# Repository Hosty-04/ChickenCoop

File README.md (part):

# Kurník

Systém pro automatizaci kurníku s detekcí snesených vajec - bakalářská práce

## Zadání

- Prostudujte možnosti automatizace uzavírání kurníku, možné metody detekce snesených vajec a dostupné možnosti komunikace a připojení zařízení do IoT sítě (např. NB-IoT, WiFi, LoRaWAN).
- Navrhněte systém pro automatické otevírání a uzavírání dvířek kurníku s možností rozšíření o jednotky se senzory ve snáškových hnízdech (min. 5 hnízd). Prostudujte možnosti napájení z akumulátoru nebo fotovoltaického panelu. Proveďte analýzu možnosti přenosu dat do cloudu a jejich zobrazení uživateli včetně historie snášek a možnosti vzdáleného ovládání, například skrze aplikaci.
- Na základě analýzy navrhněte způsob vzdálené uživatelské interakce pro zobrazení stavu dvířek, manuální ovládání a počítání snesených vajec.
- Navrhněte schéma zařízení, které bude obsahovat mikrořadič, komunikační modul, senzory, řízení dvířek, napájecí/nabíjecí obvody. Dbejte na nízký příkon celého zařízení. Proveďte návrh desky plošných spojů.
- Zkonstruujte hardwarovou realizaci navrženého systému. Osaďte a zprovozněte řídicí elektroniku. Vytvořte ovládací firmware. Realizujte přenos dat ze zařízení k uživateli včetně ovládacího rozhraní a možnosti zobrazení historie.
- Ověřte funkčnost systému experimentálním měřením a vyhodnoťte spolehlivost detekce a ovládání.
- Zveřejněte veškeré výrobní podklady na vhodné platformě (např. GitHub).

## Schémata

## Elektronika

<br>

<picture>
  <source media="(prefers-color-scheme: dark)" srcset="Schematics/block_schematic_electronics_white.png">
  <source media="(prefers-color-scheme: light)" srcset="Schematics/block_schematic_electronics_black.png">
  
</picture>

## Komunikace

<br>

<picture>
  <source media="(prefers-color-scheme: dark)" srcset="Schematics/block_schematic_comms_white.png">
  <source media="(prefers-color-scheme: light)" srcset="Schematics/block_schematic_comms_black.png">
  
</picture>

<br><br>

> Uživatelské příkazy cestují opačným směrem

## Popis

### 1) Mechanika

### a) Krabičky

Solární panel je uchycen v rámečku vytištěném z materiálu PETG, jehož vnější rozměr (360 × 240 mm) přesahuje rozměr panelu (340 × 220 mm) o 10 mm po každé straně. Tento materiál byl zvolen pro jeho vysokou houževnatost a teplotní odolnost. Kapsa pro panel je hluboká 4 mm, tedy o 1 mm více než tloušťka panelu, aby panel po vložení mírně zapadl pod úroveň okraje rámečku a nedocházelo k zadržování vody na jeho povrchu. Dno kapsy je opatřeno výřezem o rozměru 320 × 200 mm, odpovídajícím aktivní ploše panelu, takže rámeček má tvar pasparty a nestíní dopadající sluneční záření. Po vložení panelu do kapsy je spára mezi jeho okrajem a stěnou rámečku vyplněna venkovním UV odolným silikonovým tmelem, čímž vzniká vodotěsné a zároveň mechanicky pevné spojení bez nutnosti vrtat do samotného panelu. Rámeček je přišroubován přímo ke stěně kurníku vruty 6 × 80 mm s plastovými hmoždinkami 8 mm, a to přes čtyři otvory o průměru 5 mm v rozích mimo aktivní plochu panelu.

Konstrukce obsahuje jednu krabičku pro akumulátor o tloušťce stěny 2,4 mm a jednu krabičku (K) o tloušťce stěny 1,6 mm určenou pro mechaniku a elektroniku dvířek a hlavní mikrořadič. Pro každé snáškové hnízdo je dále vyhrazena samostatná krabička (Kx) se stejnou tloušťkou stěny, obsahující potřebnou elektroniku a hnízdový mikrořadič. Všechny krabičky jsou vytištěny na 3D tiskárně z materiálu PETG. Do tohoto materiálu je kvůli riziku deformace nutné vrtat při nízkých otáčkách. Zadní stěna krabiček je ve svislém směru prodloužena a má tloušťku 3,5 mm; v každém rohu této stěny jsou otvory pro vruty 4 × 40 mm, které umožňují upevnění krabiček k betonové stěně kurníku pomocí hmoždinek o průměru 6 mm. Víko je vytištěno samostatně s přesahem 2 mm; uprostřed jeho levé hrany je dutá trubička s vnitřním průměrem 2 mm. Stejná trubička je u všech krabiček na obou koncích vnější horní hrany levé stěny. Po vytištění je všemi třemi trubičkami protažen filament o průměru 1,75 mm, jehož konce se krátce nahřejí zapalovačem a roztepou do podoby hlaviček. Tím vzniká jednoduchý pant pro uchycení víka.

V krabičkách K a Kx jsou desky plošných spojů připevněny ke dnu pomocí 4 děr, šrouby vedou zeshora přes distanční sloupky a jsou zajištěny maticí. U víka krabiček jsou vytvořeny nízké drážky ve tvaru písmene U s mírně zaoblenými rohy, sloužící k protažení kabelů. Pro kabel o průřezu 1,5 mm² mají šířku 4,5 mm, hloubku 3 mm a zaoblení dna i hran 1 mm; pro kabel o průřezu 0,5 mm² šířku 3,5 mm, hloubku 2 mm a zaoblení dna i hran 0,75 mm; pro datový kabel pak šířku 6 mm, hloubku 3,5 mm a stejné zaoblení jako u prvního kabelu. Krabička pro akumulátor má zespodu dva kruhové otvory o průměru 5 mm určené pro průchod napájecích kabelů a dva větrací otvory o průměru 4 mm, umístěné v horní a spodní části tak, aby mohl uvnitř cirkulovat vzduch. Krabička Kx má zespodu jeden otvor o průměru 6 mm pro průchod kabelu od tenzometru, krabička K pak ručně vyvrtaný a zakulacený otvor o průměru 4 mm pro lanko; anténa bude položená horizontálně uvnitř krabičky.

### b) Kabeláž

Pro připojení solárního panelu a akumulátoru je použita měděná ohebná licna o průřezu 1,5 mm², připojená přes 4pinovou pružinovou WAGO svorkovnici s roztečí 5,08 mm k desce plošných spojů. Tento průřez poskytuje dostatečnou proudovou rezervu při minimálním úbytku napětí. Stejným způsobem je k desce plošných spojů připojen motor a mikrospínače, avšak za využití licny o průřezu 0,5 mm² a motor přes 2pinovou svorkovnici.

Pro datovou komunikaci byl zvolen kabel UTP CAT5e typu licna, jehož kroucené páry omezují rušení. K deskám plošných spojů je připojený přes konektory RJ45. Prodloužení vodičů tenzometru o průřezu 0,08 mm² zajišťují 4 ploché vodiče o stejné barvě a průřezu. Spojeny jsou pájkou a přes každý spoj je převlečena smršťovací bužírka s lepidlem o poměru 3:1 a rozměru 3 mm / 1 mm. K desce plošných spojů jsou připojeny přes 6pinovou pružinovou WAGO svorkovnici s roztečí 2,54 mm (možnost připojit stínění).

Kabely a vodiče jsou vedeny v klasické elektroinstalační PVC liště o rozměrech 15 × 10 mm, upevněné k betonové stěně, respektive základové desce, pomocí vrutů 3 × 30 mm a hmoždinek o průměru 5 mm. Spoje jsou utěsněny akrylovým tmelem. Speciální UV odolná lišta není pro kabely vedené po venkovní stěně kurníku potřeba, protože tato stěna je vystavena slunci pouze při jeho západu. Životnost běžné lišty se odhaduje na 5–10 let.

U prototypu jsou využity stejné kabely, vodiče a svorkovnice. Na rozdíl od finální verze jsou ale využity drátky do nepájivého pole o průřezu 0,5 mm², který plně vyhovuje proudovému odběru systému.

### c) Konstrukce

Hlavní část systému je umístěna na vnější stěně kurníku, která splňuje požadavky na umístění solárního panelu popsané v kapitole Napájení. Toto řešení zjednodušuje montáž a zároveň z velké části eliminuje vliv amoniaku ze slepičího trusu na elektroniku.

Na betonovou stěnu jsou pomocí vrutů a hmoždinek připevněny svislé dřevěné hranolky, k jejichž bočním stěnám jsou vruty upevněny hliníkové U-profily se šířkou dna 15 mm, výškou bočních stěn 15 mm, tloušťkou 1,5 mm a délkou 1 m. První vrut je umístěn na horní pozici, nad kterou se dvířka nikdy nedostanou, a druhý vrut na dolní pozici, kam dvířka nikdy nedojedou. U-profily zajišťují přesné vedení dvířek při minimálním tření. V těchto profilech se ve svislém směru pohybují nalakovaná pěněná PVC dvířka o rozměrech 24 × 35 cm a tloušťce 8 mm (pozor na výrobní tolerance). Hmotnost těchto dvířek je 350 g. Při vrtání otvorů do PVC je nutné použít nízké otáčky a nevyvíjet nadměrný přítlak. Pěněné PVC bylo zvoleno pro nízkou hmotnost, odolnost proti vlhkosti a snadnou obrobitelnost.

V horní i dolní části hranolku jsou ve svislé ose zapuštěny dva pákové koncové spínače sledující polohu dvířek. Záhlubení široká 6,5 mm a vysoká 20 mm z vnitřní strany a 15 mm z vnější strany vedou skrz hranolek a 10 mm širokou hliníkovou drážku; z vnější strany jsou kabely vyvedeny přímo do lišty. Spínače jsou upevněny vruty o průměru 2 mm. Toto provedení představuje jednoduché řešení určování krajních poloh dvířek.

Na horní části přední strany dvířek je umístěno závěsné očko M5 z nerezové oceli A2, upevněné podložkou a samojistnou maticí ze stejného materiálu; očko prochází otvorem o průměru odpovídajícím jeho metrickému závitu. Očkem je protaženo syntetické lanko (zednická šňůra) o průměru 2 mm, zajištěné dračí smyčkou zakápnutou vteřinovým lepidlem. Syntetická šňůra nekoroduje, má nízkou průtažnost a je odolná vůči vlhkosti.

Lanko vede kolmo vzhůru do krabičky K, kde je navíjeno na špulku vytištěnou z materiálu PETG (šířka 2 cm, vnější průměr 2,5 cm). Lanko je provlečeno otvorem o průměru 3 mm na okraji špulky (na straně vzdálenější od motoru) a zajištěno osmičkovým uzlem, rovněž zakápnutým vteřinovým lepidlem; uzel je zapuštěn 8 mm hluboko do záhlubení o průměru 10 mm a lanko z něj vychází na okraji záhlubení směrem k okraji špulky.

Špulka má otvor s D-profilem (průměr 3 mm, hloubka 10 mm); pomocí stavěcího šroubu (červíku) M5 z nerezové oceli A4 (délka 6 mm) a mosazné závitové vložky M5 (délka 5,8 mm, průměr 7,1 mm) je upevněna na hřídeli nízkootáčkového (20 rpm) stejnosměrného motoru s kovovou převodovkou (6 V), a to ze strany, kde vstupuje lanko. Stejnosměrný motor s převodovkou byl zvolen místo krokového motoru, protože vystačí s jednoduchým budičem, převodovka mu dává vysoký krouticí moment a polohu dvířek určují koncové spínače, takže není potřeba počítat kroky. U finální verze bude motor přes držák připevněn k hlavní desce plošných spojů.

<br>

**Tah motoru pro různé krouticí momenty**

$$
M = F \cdot r
$$

$$
F_j = \frac{M_j}{r_s} = \frac{5\ \text{N·cm}}{12,5\ \text{mm}} = 4\ \text{N} \approx \mathbf{400\ \text{g tahu}}
$$

$$
F_d = \frac{M_d}{r_s} = \frac{4\ \text{N·cm}}{12,5\ \text{mm}} = 3,2\ \text{N} \approx \mathbf{320\ \text{g tahu}}
$$

$$
F_k = \frac{M_k}{r_s} = \frac{25\ \text{N·cm}}{12,5\ \text{mm}} = 20\ \text{N} \approx \mathbf{2\ \text{kg tahu}}
$$

kde:

- $F_j$ ... síla při jmenovitém krouticím momentu
- $F_d$ ... síla při doporučeném dlouhodobém trvalém zatížení
- $F_k$ ... síla při maximálním krátkodobém zatížení
- $M_j$ ... jmenovitý krouticí moment
- $M_d$ ... krouticí moment při doporučeném dlouhodobém trvalém zatížení
- $M_k$ ... krouticí moment při maximálním krátkodobém zatížení
- $r_s$ ... poloměr špulky

Dvířka o hmotnosti 350 g představují mírně vyšší zátěž, než je doporučené trvalé zatížení, tudíž lze očekávat pokles otáček motoru na 15–17 ot./min. Počítá se i s rezervou pro případ mírného drhnutí dvířek v drážkách. Nízkootáčkový motor spolu s menším vnějším průměrem špulky byl zvolen pro zvýšení síly motoru a snížení rizika přetrhnutí lanka nebo vykolejení dvířek.

<br>

Otvor pro mosaznou závitovou vložku má průměr 8 mm a v posledních 6,5 mm směrem ke hřídeli se zužuje na 6,5 mm. Vložka se do otvoru zavede pomocí 16mm šroubu M5; jakmile narazí na zúženou část otvoru, hlava šroubu se nahřeje mikropájkou, plast se v místě zúžení roztaví a umožní zalisování vložky. Po odejmutí pájky plast opět ztuhne a vložku pevně ukotví.

Vedlejší část systému tvoří spádovaná snášková hnízda s košíkem, orientovaná příčně ke stěně. Celá konstrukce musí být od stěny vzdálena natolik, aby se jí nikde nedotýkala a zároveň za ní zůstal prostor pro vedení kabelu. Návrh je koncipován tak, aby se do prostoru s tenzometrem nemohli dostat ani ti nejmenší hlodavci — rozměr základové desky a výška lišt jsou klíčové.

Pod hnízda je vruty (na vyšší straně hnízda přes dřevěné kvantlíky) připevněna voděodolná OSB 3 deska o rozměrech 37 × 28 cm a tloušťce 12 mm. Další deska (37-1,2-0,2 × 28-1,2-0,2 cm, stejná tloušťka) tvoří základovou desku a je připevněna k podlaze kurníku; třetí deska stejné tloušťky, o rozměrech 40 × 50 cm, slouží jako zadní stěna. Řezné hrany desek jsou natřeny lakem. Mezi horní a spodní deskou je u stěny umístěn tenzometr o tloušťce 12,7 mm, orientovaný kratší stranou s vodiči směrem ke stěně. Tenzometr váží s přesností 2 g, což pro vejce o hmotnosti 50–70 g plně postačuje, a je dimenzován na zatížení 20 kg — maximální předpokládané zatížení (dvě desky, hnízdo, dvě slepice a deset vajec) přitom činí přibližně 10 kg. Volný i pevný konec tenzometru je upevněn dvěma zápustnými imbusovými šrouby M5 z nerezové oceli A2, procházejícími vážicí, respektive základovou deskou skrz otvory o průměru 4,5 mm a zapuštěnými do záhlubení o průměru 10 mm a hloubce 3 mm; hlava šroubu je u vážicí desky zalita akrylovým tmelem. Použité šrouby mají délku 25 mm. Mezi deskami a závity tenzometru jsou umístěny distanční matice M6 z nerezové oceli A2 o tloušťce 4 mm.

Optická závora není pro počítání vajec v kurníku vhodná mimo jiné kvůli prachu, peří, podestýlce a zvědavým slepicím, jejichž přítomnost by mohla přerušit laserový paprsek a být chybně vyhodnocena jako propadnuté vejce. Z tohoto důvodu byl pro detekci vajec zvolen tenzometr.

Ze zbytku OSB desky jsou vyrobeny ochranné lišty, přišroubované zeshora po bocích základové desky. Lišty jsou vysoké 21,5 mm, protože vzdálenost mezi deskami činí 20,7 mm a celá horní konstrukce musí být podepřena pouze tenzometrem — zároveň musí zůstat zachována vůle alespoň 3 mm. Do zadní lišty je vyvrtán otvor, kterým prochází již prodloužený kabel od tenzometru; kabel nesmí být mechanicky namáhán tahem. Kabel dále vede vzhůru po stěně do krabičky Kx, odkud je z boku vyveden datový kabel, vedoucí vysoko po stěně až do krabičky K. Uprostřed konstrukce, naproti košíku, je vytvořen stavitelný doraz pomocí zápustného imbusového šroubu M5 z nerezové oceli A2 (délka 30 mm), procházejícího spodní deskou skrz otvor o průměru 4,5 mm a zapuštěného do záhlubení o průměru 10 mm a hloubce 6 mm. Doraz tvoří mosazná kloboučková matice M5 (délka 10 mm, délka závitu 7,5 mm), zvolená kvůli omezení ulpívání nečistot. Optimální vůle dorazu je 0,8 mm, což odpovídá jedné otáčce šroubu M5 nebo přibližně tloušťce běžné platební karty.

### 2) Řízení

Hlavní řídicí jednotkou systému je mikrořadič LoRa-E5 mini (M) se STM32WLE5JC a integrovaným LoRa modulem, komunikujícím přes LoRaWAN stack. Technologie LoRaWAN umožňuje na rozdíl od Wi-Fi komunikaci na velké vzdálenosti při nízké spotřebě energie a na rozdíl od NB-IoT trvalé řešení s dobrým pokrytím. U každého snáškového hnízda je umístěn úsporný mikrořadič STM32 NUCLEO-L031K6 (Mx); vlastní řadič v každém hnízdě zkracuje citlivé analogové vedení od tenzometru a usnadňuje přidání dalších hnízd. K programování slouží programátor ST-Link V2. Před programováním je potřeba programátor připojit k dané desce klasickými kabely DuPont — stačí propojit piny 3V3, SWCLK, SWDIO, GND a nRST. U finální verze jsou desky osazeny v paticích (dutinkových lištách).

Firmware je vyvíjen v prostředí Visual Studio Code s rozšířením STM32CubeIDE a využívá knihovny HAL. U LoRa-E5 mini je potřeba nejprve odstranit tovární AT firmware. Součástí firmwaru hlavního mikrořadiče jsou astronomické hodiny, jež pomocí RTC obvodu počítají čas východu a západu slunce; podle těchto údajů se pak automaticky otevírají a zavírají dvířka kurníku. Z kalendáře dokáže řadič určit i roční období. Prostý časovač nebyl zvolen kvůli proměnlivé délce dne a světelný senzor byl zavržen, protože by mohl vyvolat chybné sepnutí motoru dvířek při zatažené obloze (déšť, bouřka) nebo vlivem pouličního osvětlení či světlometů automobilů.

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
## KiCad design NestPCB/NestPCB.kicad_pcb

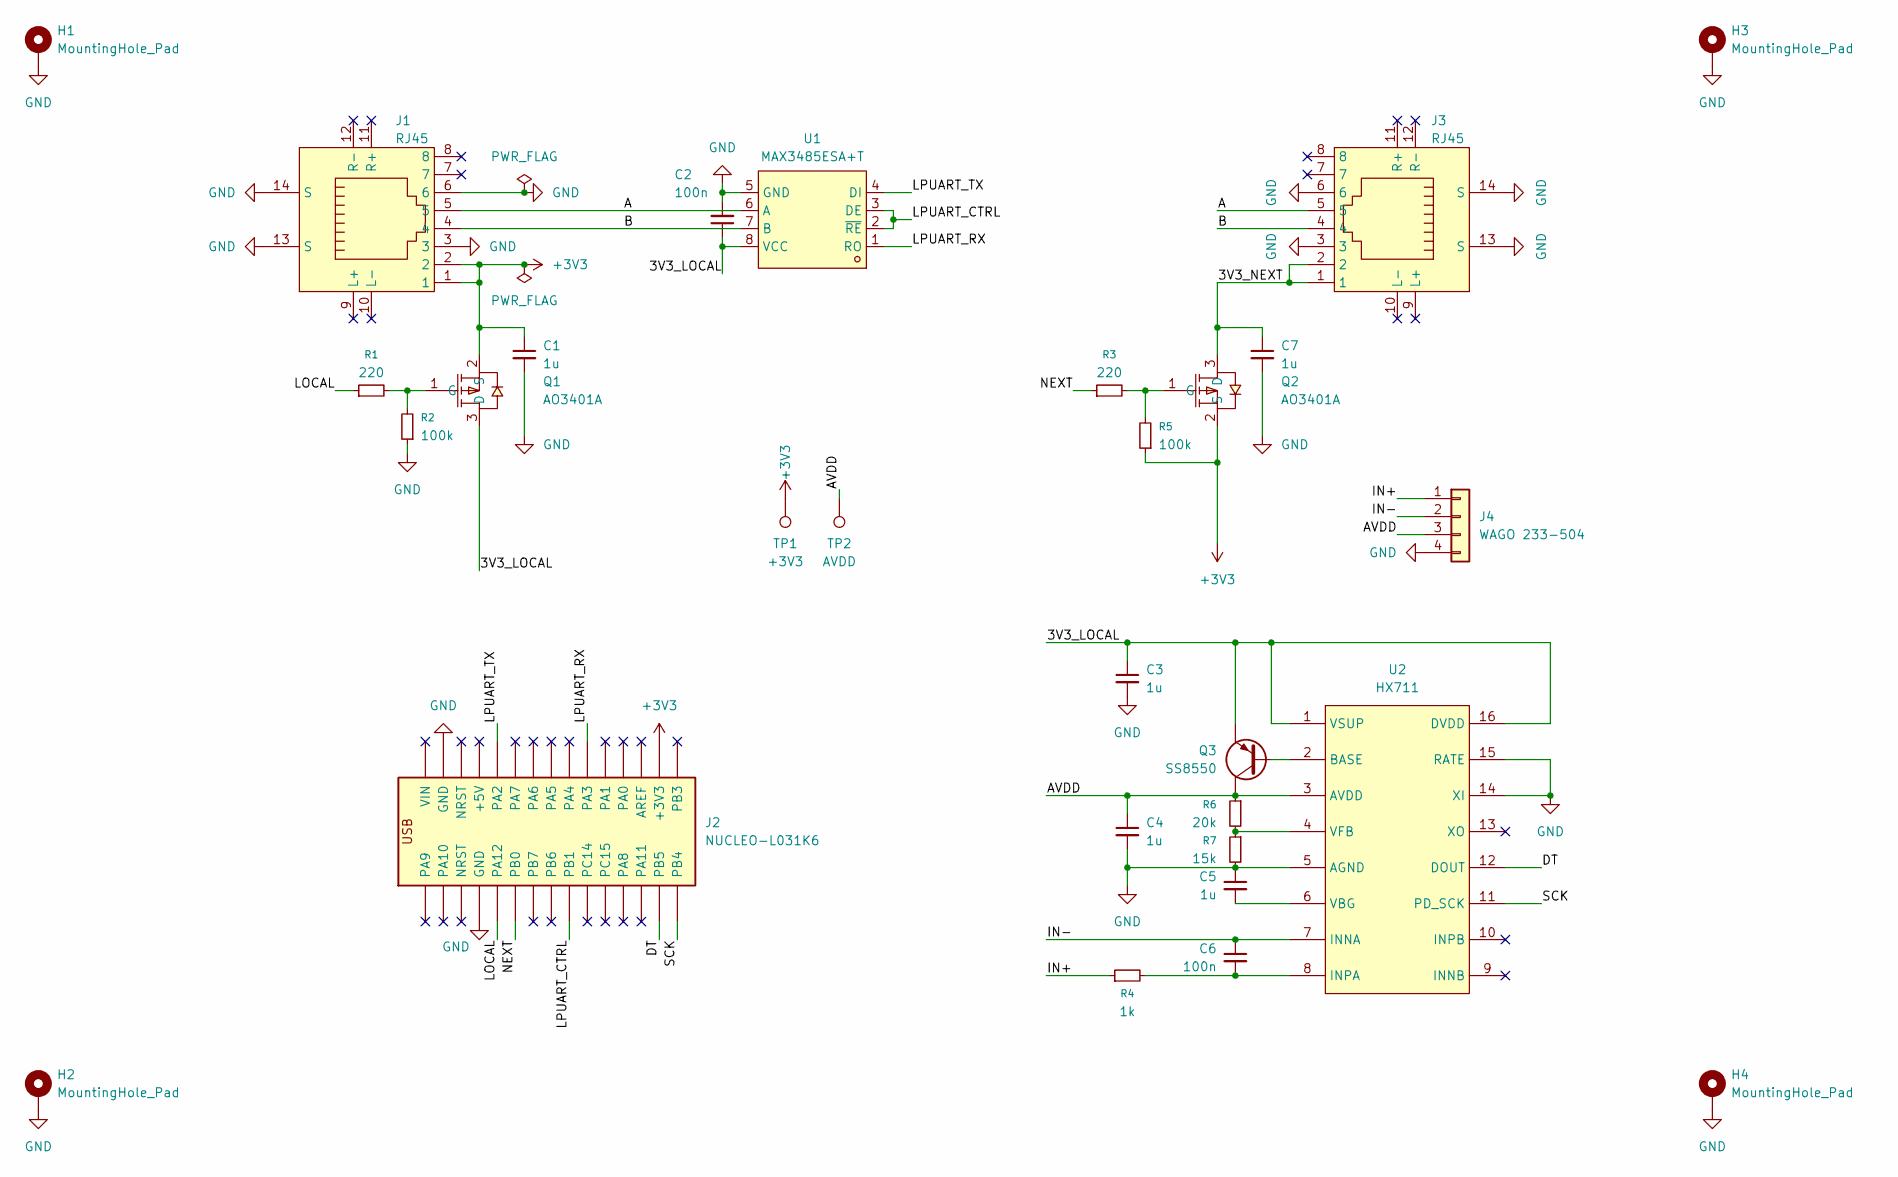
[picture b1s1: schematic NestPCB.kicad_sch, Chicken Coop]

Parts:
C1, C3, C4, C5, C7: 1u; C_0805_2012Metric
C2, C6: 100n; C_0805_2012Metric
H1, H2, H3, H4: MountingHole_Pad; MountingHole_3.2mm_M3_Pad
J1, J3: RJ45; RJ45-TH_R-RJ45R08P-C000; MPN R-RJ45R08P-C000; LCSC Part C386757
J2: NUCLEO-L031K6
J4: WAGO 233-504; CONN-TH_233-504
Q1, Q2: AO3401A; SOT-23_L2.9-W1.3-P1.90-LS2.4-BR; MPN AO3401A; LCSC Part C15127
Q3: SS8550; SOT-23-3_L2.9-W1.3-P1.90-LS2.4-BR; MPN SS8550 Y2(RANGE:200-350); LCSC Part C8542
R1, R3: 220; R_0805_2012Metric
R2, R5: 100k; R_0805_2012Metric
R4: 1k; R_0805_2012Metric
R6: 20k; R_0805_2012Metric
R7: 15k; R_0805_2012Metric
TP1: +3V3; TestPoint_THTPad_D2.0mm_Drill1.0mm
TP2: AVDD; TestPoint_THTPad_D2.0mm_Drill1.0mm
U1: MAX3485ESA+T; SOIC-8_L4.9-W3.9-P1.27-LS6.0-BL; MPN MAX3485ESA+T; LCSC Part C18148
U2: HX711; SOP-16_L10.0-W3.9-P1.27-LS6.0-BL; MPN HX711; LCSC Part C43656

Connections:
+3V3: C1.1, J1.1, J1.2, J2.CN4-14 (+3V3), Q1.2 (S), Q2.2 (S), R5.1, TP1.1
/3V3_LOCAL: C2.1, C3.1, Q1.3 (D), Q3.2 (E), U1.8 (VCC), U2.1 (VSUP), U2.16 (DVDD)
/3V3_NEXT: C7.1, J3.1, J3.2, Q2.3 (D)
/A: J1.5, J3.5, U1.6 (A)
/AVDD: C4.1, J4.3, Q3.3 (C), R6.1, TP2.1, U2.3 (AVDD)
/B: J1.4, J3.4, U1.7 (B)
/DT: J2.CN3-14 (PB5), U2.12 (DOUT)
/IN+: J4.1, R4.1
/IN-: C6.1, J4.2, U2.7 (INNA)
/LOCAL: J2.CN3-5 (PA12), R1.1
/LPUART_CTRL: J2.CN3-9 (PB1), U1.2 (~RE), U1.3 (DE)
/LPUART_RX: J2.CN4-10 (PA3), U1.1 (RO)
/LPUART_TX: J2.CN4-5 (PA2), U1.4 (DI)
/NEXT: J2.CN3-6 (PB0), R3.1
/SCK: J2.CN3-15 (PB4), U2.11 (PD_SCK)
GND: C1.2, C2.2, C3.2, C4.2, C5.1, C7.2, H1.1, H2.1, H3.1, H4.1, J1.3, J1.6, J1.13 (S), J1.14 (S), J2.CN3-4 (GND), J2.CN4-2 (GND), J3.3, J3.6, J3.13 (S), J3.14 (S), J4.4, R2.1, R7.2, U1.5 (GND), U2.5 (AGND), U2.14 (XI), U2.15 (RATE)
unnamed: Q1.1 (G), R1.2, R2.2
unnamed: Q2.1 (G), R3.2, R5.2
unnamed: Q3.1 (B), U2.2 (BASE)
unnamed: C6.2, R4.2, U2.8 (INPA)
unnamed: C5.2, U2.6 (VBG)
unnamed: R6.2, R7.1, U2.4 (VFB)

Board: 2 copper layers, 29 parts (0 on the bottom side), 22 nets, no tracks yet.

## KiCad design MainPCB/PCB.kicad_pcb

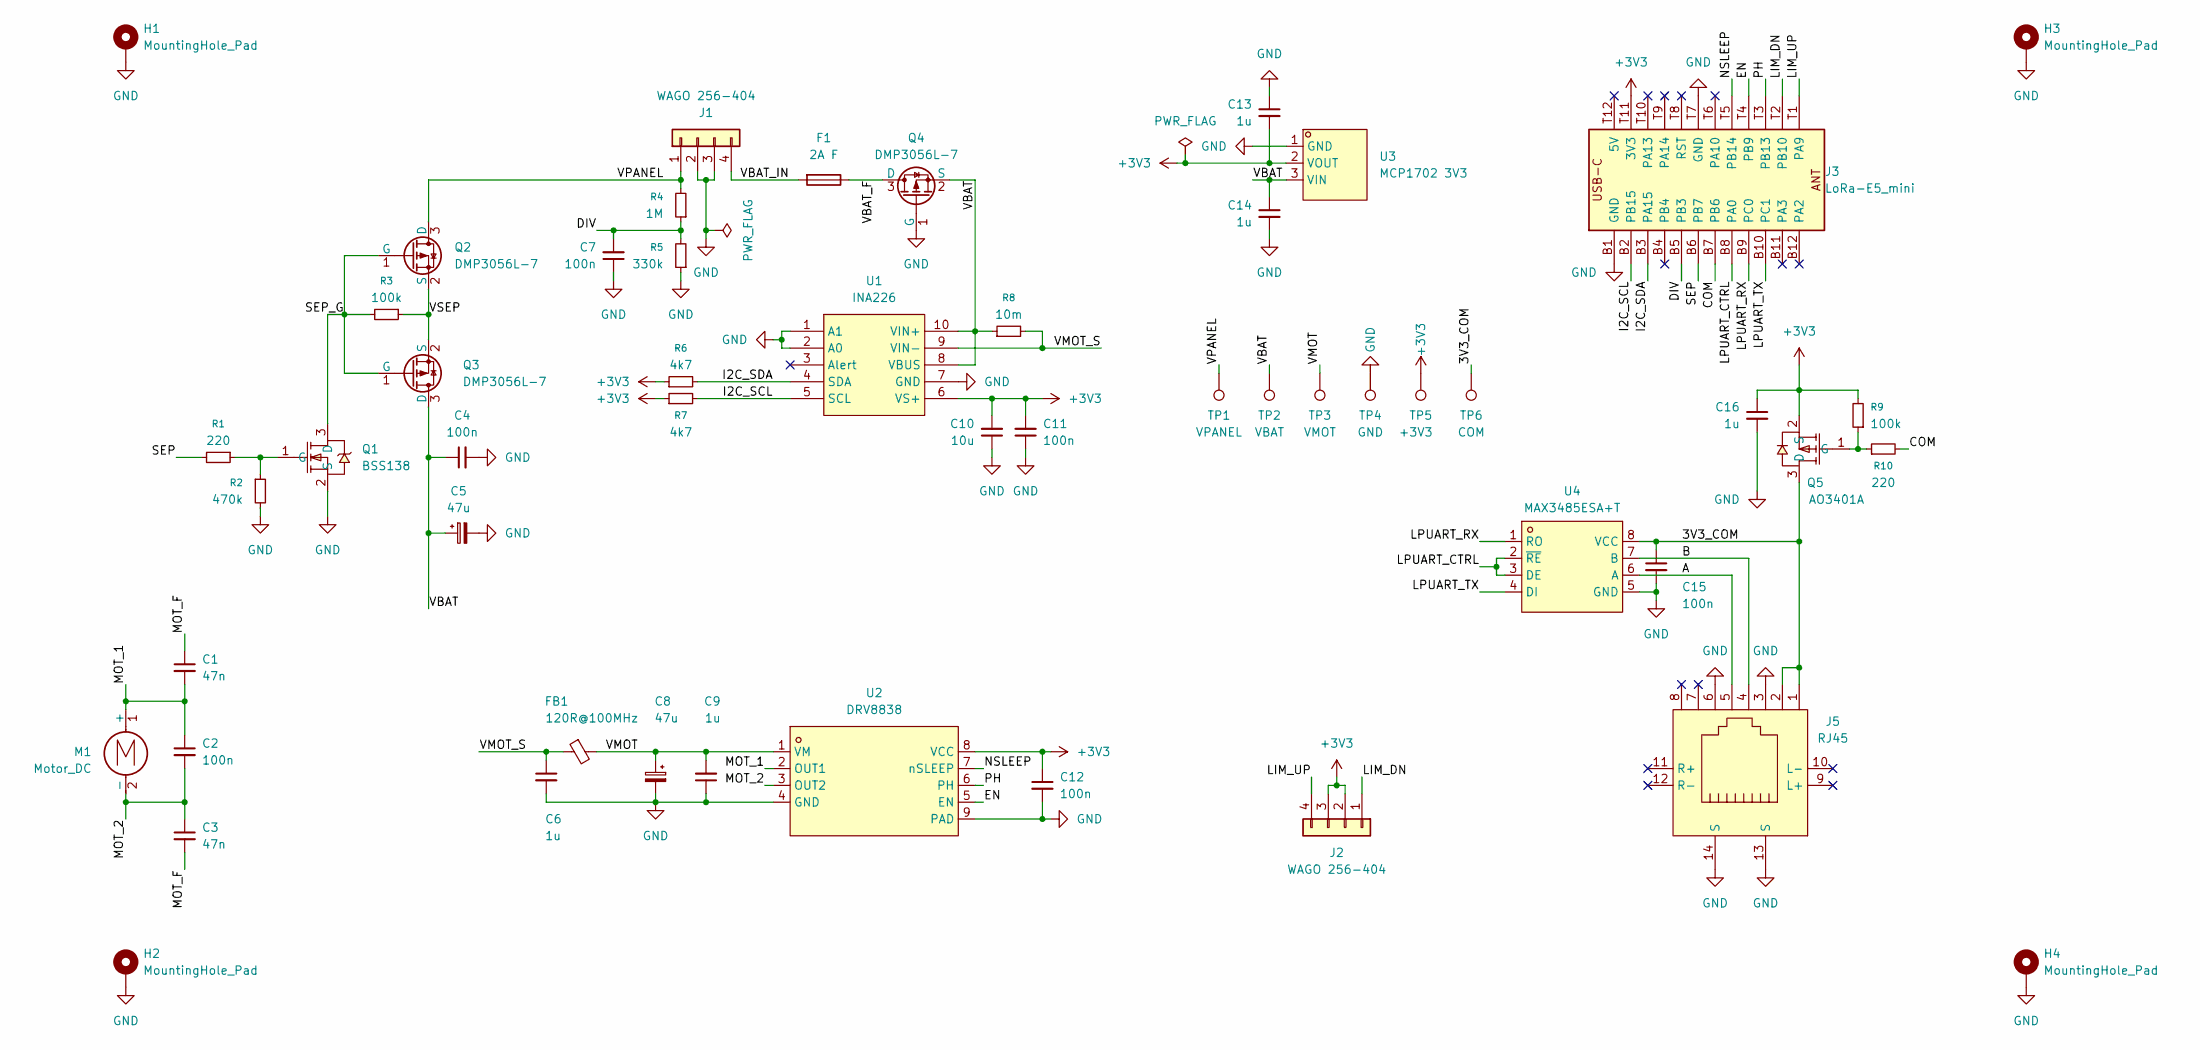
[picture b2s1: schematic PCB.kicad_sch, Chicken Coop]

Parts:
C1, C3: 47n; C_0805_2012Metric
C2, C4, C7, C11, C12, C15: 100n; C_0805_2012Metric
C5, C8: 47u; CP_Elec_6.3x5.8
C6, C9, C13, C14, C16: 1u; C_0805_2012Metric
C10: 10u; C_0805_2012Metric
F1: 2A F; FUSE-TH_L22.0-W9.0-P22.60
FB1: 120R@100MHz; L_0805_2012Metric
H1, H2, H3, H4: MountingHole_Pad; MountingHole_3.2mm_M3_Pad
J1, J2: WAGO 256-404; CONN-TH_4P-P5.08-256-404
J3: LoRa-E5_mini
J5: RJ45; RJ45-TH_R-RJ45R08P-C000; MPN R-RJ45R08P-C000; LCSC Part C386757
M1: Motor_DC; Pololu_MicroMotor_Bracket
Q1: BSS138; SOT-23-3_L2.9-W1.6-P1.90-LS2.8-BR; MPN BSS138; LCSC Part C52895
Q2, Q3, Q4: DMP3056L-7; SOT-23; MPN DMP3056L-7; LCSC Part C150724
Q5: AO3401A; SOT-23_L2.9-W1.3-P1.90-LS2.4-BR; MPN AO3401A; LCSC Part C15127
R1, R10: 220; R_0805_2012Metric
R2: 470k; R_0805_2012Metric
R3, R9: 100k; R_0805_2012Metric
R4: 1M; R_0805_2012Metric
R5: 330k; R_0805_2012Metric
R6, R7: 4k7; R_0805_2012Metric
R8: 10m; R_1206_3216Metric
TP1: VPANEL; TestPoint_THTPad_D2.0mm_Drill1.0mm
TP2: VBAT; TestPoint_THTPad_D2.0mm_Drill1.0mm
TP3: VMOT; TestPoint_THTPad_D2.0mm_Drill1.0mm
TP4: GND; TestPoint_THTPad_D2.0mm_Drill1.0mm
TP5: +3V3; TestPoint_THTPad_D2.0mm_Drill1.0mm
TP6: COM; TestPoint_THTPad_D2.0mm_Drill1.0mm
U1: INA226; MSOP-10_L3.0-W3.0-P0.50-LS5.0-BL; MPN INA226AIDGSR; LCSC Part C49851
U2: DRV8838; WSON-8_L2.0-W2.0-P0.50-TL-EP; MPN DRV8838DSGR; LCSC Part C86667
U3: MCP1702 3V3; SOT-23-3_L2.9-W1.3-P1.90-LS2.4-BR; MPN MCP1702T-3302E/CB; LCSC Part C33844
U4: MAX3485ESA+T; SOIC-8_L4.9-W3.9-P1.27-LS6.0-BL; MPN MAX3485ESA+T; LCSC Part C18148

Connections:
+3V3: C10.2, C11.2, C12.1, C13.2, C16.1, J2.2, J2.3, J3.T11 (3V3), Q5.2 (S), R6.1, R7.1, R9.2, TP5.1, U1.6 (VS+), U2.8 (VCC), U3.2 (VOUT)
/3V3_COM: C15.1, J5.1, J5.2, Q5.3 (D), TP6.1, U4.8 (VCC)
/A: J5.5, U4.6 (A)
/B: J5.4, U4.7 (B)
/COM: J3.B7 (PB6), R10.2
/DIV: C7.2, J3.B5 (PB3), R4.1, R5.2
/EN: J3.T4 (PB9), U2.5 (EN)
/I2C_SCL: J3.B2 (PB15), R7.2, U1.5 (SCL)
/I2C_SDA: J3.B3 (PA15), R6.2, U1.4 (SDA)
/LIM_DN: J2.1, J3.T2 (PB10)
/LIM_UP: J2.4, J3.T1 (PA9)
/LPUART_CTRL: J3.B8 (PA0), U4.2 (~RE), U4.3 (DE)
/LPUART_RX: J3.B9 (PC0), U4.1 (RO)
/LPUART_TX: J3.B10 (PC1), U4.4 (DI)
/MOT_1: C1.2, C2.1, M1.1 (+), U2.2 (OUT1)
/MOT_2: C2.2, C3.1, M1.2 (-), U2.3 (OUT2)
/NSLEEP: J3.T5 (PB14), U2.7 (nSLEEP)
/PH: J3.T3 (PB13), U2.6 (PH)
/SEP: J3.B6 (PB7), R1.2
/SEP_G: Q1.3 (D), Q2.1 (G), Q3.1 (G), R3.2
/VBAT: C4.1, C5.1, C14.1, Q3.3 (D), Q4.2 (S), R8.1, TP2.1, U1.8 (VBUS), U1.10 (VIN+), U3.3 (VIN)
/VBAT_F: F1.1, Q4.3 (D)
/VBAT_IN: F1.2, J1.4
/VMOT: C8.1, C9.2, FB1.2, TP3.1, U2.1 (VM)
/VMOT_S: C6.1, FB1.1, R8.2, U1.9 (VIN-)
/VPANEL: J1.1, Q2.3 (D), R4.2, TP1.1
/VSEP: Q2.2 (S), Q3.2 (S), R3.1
GND: C4.2, C5.2, C6.2, C7.1, C8.2, C9.1, C10.1, C11.1, C12.2, C13.1, C14.2, C15.2, C16.2, H1.1, H2.1, H3.1, H4.1, J1.2, J1.3, J3.B1 (GND), J3.T7 (GND), J5.3, J5.6, J5.13 (S), J5.14 (S), Q1.2 (S), Q4.1 (G), R2.2, R5.1, TP4.1, U1.1 (A1), U1.2 (A0), U1.7 (GND), U2.4 (GND), U2.9 (PAD), U3.1 (GND), U4.5 (GND)
unnamed: C1.1, C3.2
unnamed: Q1.1 (G), R1.1, R2.1
unnamed: Q5.1 (G), R9.1, R10.1

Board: 2 copper layers, 49 parts (0 on the bottom side), 30 nets, no tracks yet.

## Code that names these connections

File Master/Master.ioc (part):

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Mcu.Name=STM32WLE5JCIx
Mcu.Package=UFBGA73
Mcu.UserName=STM32WLE5JCIx
PA0.GPIOParameters=GPIO_Label
PA0.GPIO_Label=LPUART_CTRL
PA0.Signal=GPIO_Analog
PA13.GPIOParameters=GPIO_Label
PA13.GPIO_Label=DEBUG_SWDIO
PA13.Mode=Serial_Wire
PA13.Signal=DEBUG_JTMS-SWDIO
PA14.GPIOParameters=GPIO_Label
PA14.GPIO_Label=DEBUG_SWCLK
PA14.Mode=Serial_Wire
PA14.Signal=DEBUG_JTCK-SWCLK
PA15.GPIOParameters=GPIO_Label
PA15.GPIO_Label=I2C_SDA
PA15.Mode=I2C
PA15.Signal=I2C2_SDA
PA2.GPIOParameters=GPIO_Label
PA2.GPIO_Label=USART_TX
PA2.Mode=Asynchronous
PA2.Signal=USART2_TX
PA3.GPIOParameters=GPIO_Label
PA3.GPIO_Label=USART_RX
PA3.Mode=Asynchronous
PA3.Signal=USART2_RX
PA4.GPIOParameters=GPIO_Label
PA4.GPIO_Label=RF_CTRL1
PA4.Signal=GPIO_Output
PA5.GPIOParameters=GPIO_Label
PA5.GPIO_Label=RF_CTRL2
PA5.Signal=GPIO_Output
PA9.GPIOParameters=GPIO_Label
PA9.GPIO_Label=LIM_UP
PA9.Signal=GPIO_Analog
PB0-VDD_TCXO.Mode=HSE-TCXO
PB0-VDD_TCXO.Signal=VDDTCXO
PB10.GPIOParameters=GPIO_Label
PB10.GPIO_Label=LIM_DN
PB10.Signal=GPIO_Analog
PB13.GPIOParameters=GPIO_Label
PB13.GPIO_Label=PH
PB13.Signal=GPIO_Analog
PB14.GPIOParameters=GPIO_Label
PB14.GPIO_Label=NSLEEP
PB14.Signal=GPIO_Analog
PB15.GPIOParameters=GPIO_Label
PB15.GPIO_Label=I2C_SCL
PB15.Mode=I2C
PB15.Signal=I2C2_SCL
PB3.GPIOParameters=GPIO_Label
PB3.GPIO_Label=DIV
PB3.Mode=IN2
PB3.Signal=ADC_IN2
PB6.GPIOParameters=PinState,GPIO_Label
PB6.GPIO_Label=COM
PB6.PinState=GPIO_PIN_SET
PB6.Signal=GPIO_Output
PB7.GPIOParameters=PinState,GPIO_Label
PB7.GPIO_Label=SEP
PB7.PinState=GPIO_PIN_SET
PB7.Signal=GPIO_Output
PB9.GPIOParameters=GPIO_Label
PB9.GPIO_Label=EN
PB9.Signal=S_TIM17_CH1
PC0.GPIOParameters=GPIO_Label
PC0.GPIO_Label=LPUART_RX
PC0.Mode=Asynchronous
PC0.Signal=LPUART1_RX
PC1.GPIOParameters=GPIO_Label
PC1.GPIO_Label=LPUART_TX
PC1.Mode=Asynchronous
PC1.Signal=LPUART1_TX
PC14-OSC32_IN.Mode=LSE-External-Oscillator
PC14-OSC32_IN.Signal=RCC_OSC32_IN
PC15-OSC32_OUT.Mode=LSE-External-Oscillator
PC15-OSC32_OUT.Signal=RCC_OSC32_OUT
RCC.HSE_VALUE=32000000
RCC.SYSCLKFreq_VALUE=48000000
RCC.SYSCLKSource=RCC_SYSCLKSOURCE_PLLCLK
board=custom

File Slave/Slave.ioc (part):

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Mcu.Name=STM32L031K(4-6)Tx
Mcu.Package=LQFP32
Mcu.UserName=STM32L031K6Tx
PA12.GPIOParameters=GPIO_Label
PA12.GPIO_Label=LOCAL
PA12.Signal=GPIO_Output
PA13.Mode=Serial_Wire
PA13.Signal=SYS_SWDIO
PA14.Mode=Serial_Wire
PA14.Signal=SYS_SWCLK
PA2.GPIOParameters=GPIO_Label
PA2.GPIO_Label=LPUART_TX
PA2.Mode=Asynchronous
PA2.Signal=LPUART1_TX
PA3.GPIOParameters=GPIO_PuPd,GPIO_Label
PA3.GPIO_Label=LPUART_RX
PA3.GPIO_PuPd=GPIO_PULLUP
PA3.Mode=Asynchronous
PA3.Signal=LPUART1_RX
PB0.GPIOParameters=PinState,GPIO_Label
PB0.GPIO_Label=NEXT
PB0.PinState=GPIO_PIN_SET
PB0.Signal=GPIO_Output
PB1.GPIOParameters=GPIO_Label
PB1.GPIO_Label=LPUART_CTRL
PB1.Mode=Hardware Flow Control (RS485)
PB1.Signal=LPUART1_DE
PB4.GPIOParameters=GPIO_Label
PB4.GPIO_Label=SCK
PB4.Signal=GPIO_Output
PB5.GPIOParameters=GPIO_Label
PB5.GPIO_Label=DT
PB5.Signal=GPIO_Input
RCC.HSE_VALUE=8000000
RCC.SYSCLKFreq_VALUE=2097000
board=custom
